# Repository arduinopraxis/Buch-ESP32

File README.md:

# Buch-ESP32 Mikrocontroller Praxiseinstieg
Buch ESP32 Mikrocontroller Praxiseinstieg von Thomas Brühlmann

Verlag MITP ([https://www.mitp.de/Unsere-Autoren/Thomas-Bruehlmann/ESP32-Mikrocontroller-Praxiseinstieg.html])

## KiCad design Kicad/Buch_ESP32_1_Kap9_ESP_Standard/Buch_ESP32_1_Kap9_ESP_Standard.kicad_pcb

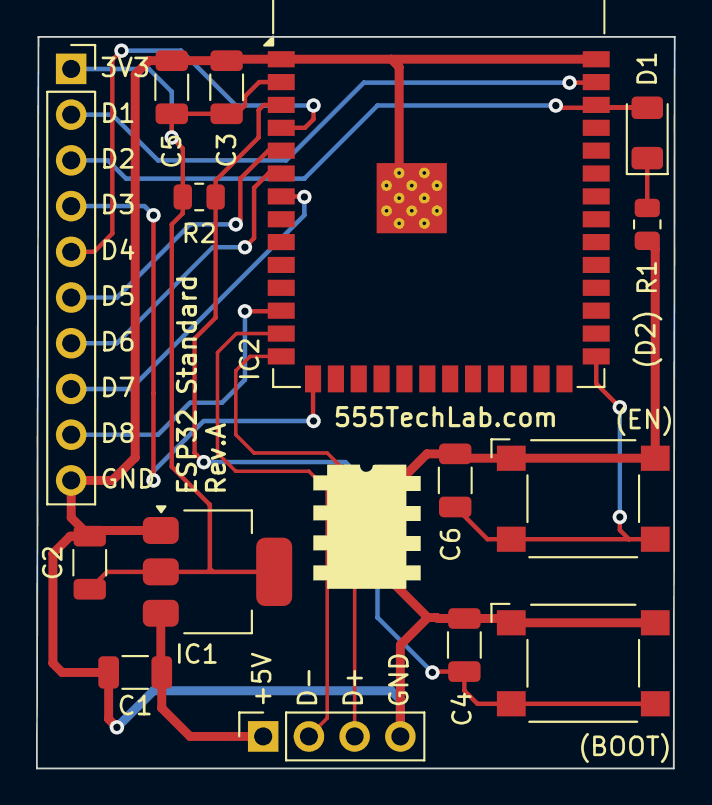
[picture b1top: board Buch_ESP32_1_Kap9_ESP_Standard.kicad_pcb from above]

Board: 2 copper layers, 35.4 x 40.6 mm, 15 parts (0 on the bottom side), 16 nets.

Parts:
C1, C2, C3, C4, C5, C6: 0.1uF; C_1206_3216Metric
D1: LED; LED_1206_3216Metric
IC1: AMS1117-3.3; SOT-223-3_TabPin2
IC2: ESP32-S3-WROOM-1
J1: Conn_01x10_Pin; PinSocket_1x10_P2.54mm_Vertical
J3: Conn_01x04_Socket; PinSocket_1x04_P2.54mm_Vertical
R1, R2: R_Small; R_0805_2012Metric
SW1, SW2: SW_Push; SW_SPST_Omron_B3FS-105xP

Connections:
+3V3: C2.1, C3.1, C5.1, IC1.2 (VO), IC2.2 (3V3), J1.1, R2.1
+5V: C1.1, IC1.3 (VI), J3.1
BOOT: C6.1, IC2.27 (IO0), SW2.2
D1: IC2.39 (IO1), J1.2
D2: D1.2 (A), IC2.38 (IO2), J1.3
D3: IC2.15 (IO3), J1.4
D4: IC2.4 (IO4), J1.5
D5: IC2.5 (IO5), J1.6
D6: IC2.6 (IO6), J1.7
D7: IC2.7 (IO7), J1.8
D8: IC2.12 (IO8), J1.9
EN: C4.1, IC2.3 (EN), R2.2, SW1.2
GND: C1.2, C2.2, C3.2, C4.2, C5.2, C6.2, IC1.1 (GND), IC2.1 (GND), IC2.40 (GND), IC2.41 (GND), J1.10, J3.4, R1.2, SW1.1, SW2.1
unnamed: D1.1 (K), R1.1
USB_N: IC2.13 (IO19), J3.2
USB_P: IC2.14 (IO20), J3.3

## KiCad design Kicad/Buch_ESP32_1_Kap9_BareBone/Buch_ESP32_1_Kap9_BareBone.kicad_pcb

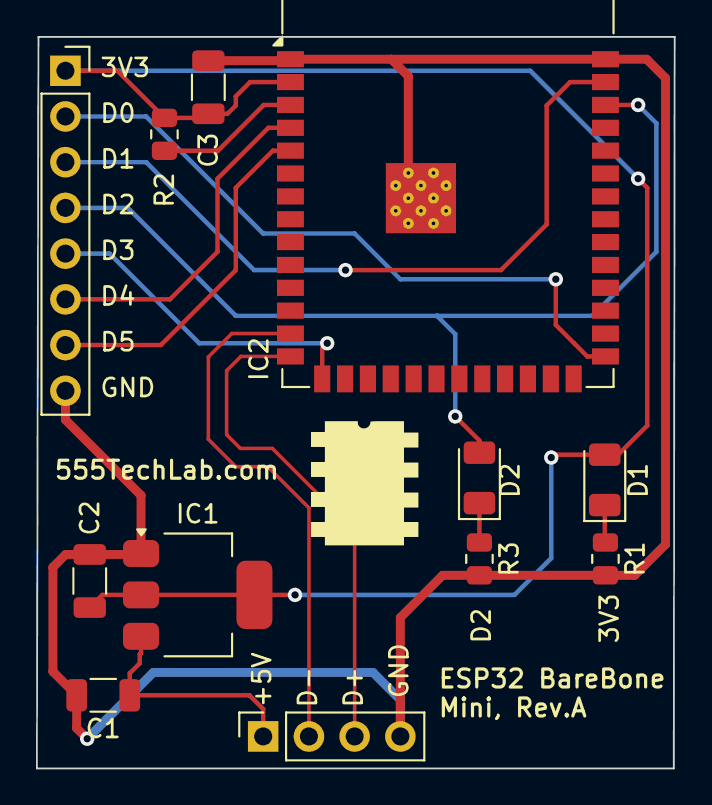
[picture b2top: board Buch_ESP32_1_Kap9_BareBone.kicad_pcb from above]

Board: 2 copper layers, 35.4 x 40.6 mm, 12 parts (0 on the bottom side), 14 nets.

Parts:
C1, C2, C3: 0.1uF; C_1206_3216Metric
D1, D2: LED; LED_1206_3216Metric
IC1: AMS1117-3.3; SOT-223-3_TabPin2
IC2: ESP32-S3-WROOM-1
J2: Conn_01x08_Pin; PinSocket_1x08_P2.54mm_Vertical
J3: Conn_01x04_Socket; PinSocket_1x04_P2.54mm_Vertical
R1, R2, R3: R_Small; R_0805_2012Metric

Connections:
+3V3: C2.1, C3.1, D1.2 (A), IC1.2 (VO), IC2.2 (3V3), J2.1, R2.1
+5V: C1.1, IC1.3 (VI), J3.1
D0: IC2.27 (IO0), J2.2
D1: IC2.39 (IO1), J2.3
D2: D2.2 (A), IC2.38 (IO2), J2.4
D3: IC2.15 (IO3), J2.5
D4: IC2.4 (IO4), J2.6
D5: IC2.5 (IO5), J2.7
GND: C1.2, C2.2, C3.2, IC1.1 (GND), IC2.1 (GND), IC2.40 (GND), IC2.41 (GND), J2.8, J3.4, R1.2, R3.2
unnamed: D1.1 (K), R1.1
unnamed: D2.1 (K), R3.1
unnamed: IC2.3 (EN), R2.2
USB_N: IC2.13 (IO19), J3.2
USB_P: IC2.14 (IO20), J3.3
